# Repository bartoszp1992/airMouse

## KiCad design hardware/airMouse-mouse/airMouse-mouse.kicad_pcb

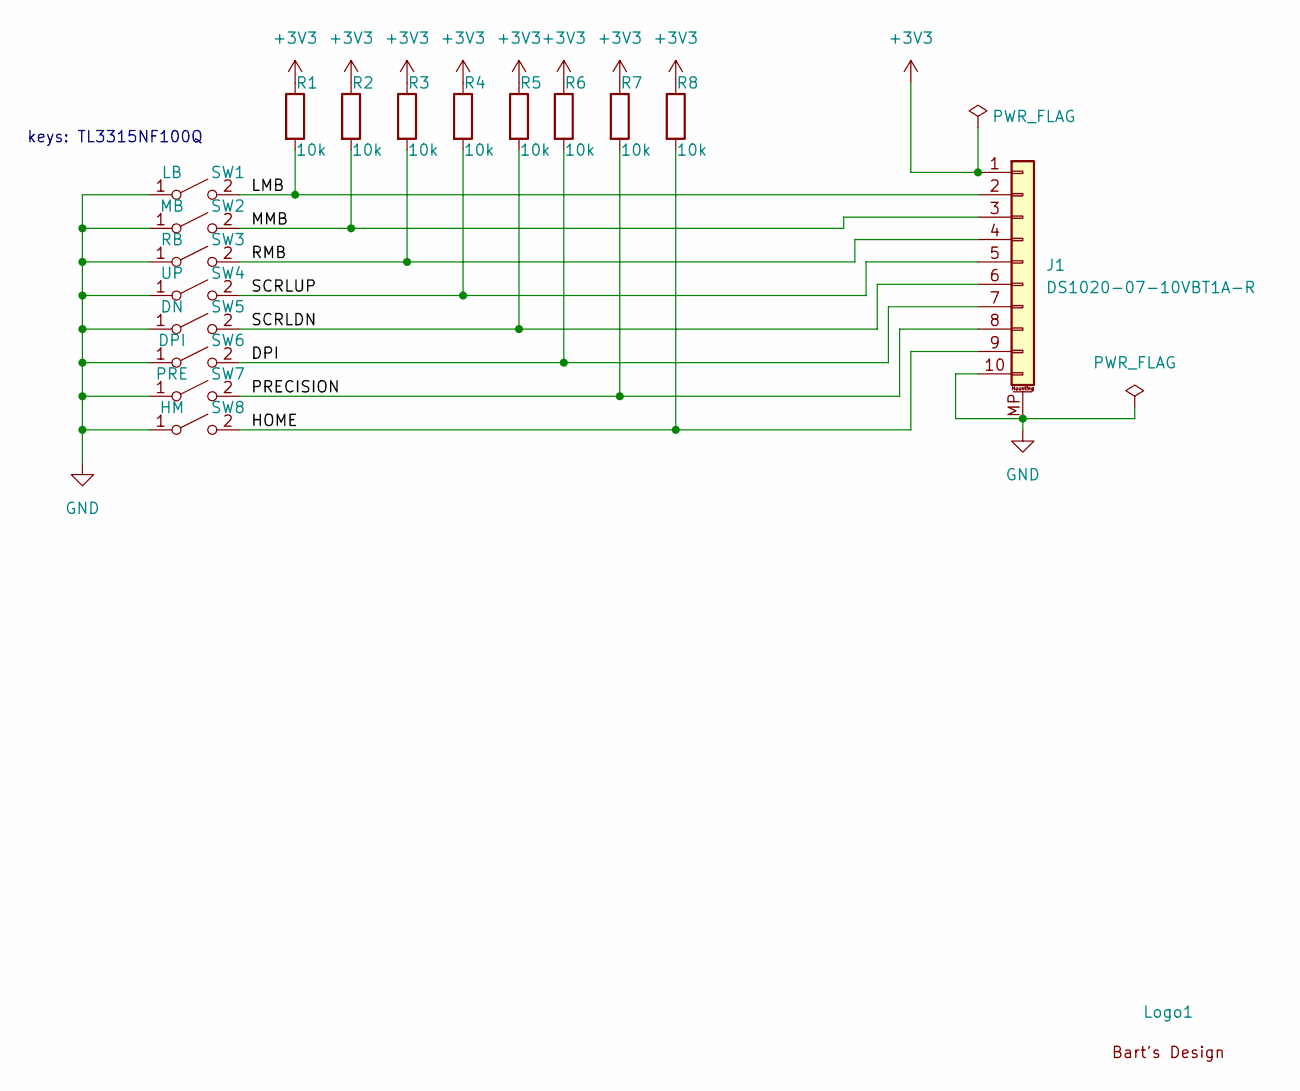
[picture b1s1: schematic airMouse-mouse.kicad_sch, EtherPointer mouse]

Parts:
J1: DS1020-07-10VBT1A-R
Logo1: Bart's Design 30mm
R1, R2, R3, R4, R5, R6, R7, R8: 10k; R_0603_1608Metric
SW1, SW2, SW3, SW4, SW5, SW6, SW7, SW8: KEY; TL3315NF100Q

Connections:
+3V3: J1.1, R1.1, R2.1, R3.1, R4.1, R5.1, R6.1, R7.1, R8.1
/DPI: J1.7, R6.2, SW6.2 (B)
/HOME: J1.9, R8.2, SW8.2 (B)
/LMB: J1.2, R1.2, SW1.2 (B)
/MMB: J1.3, R2.2, SW2.2 (B)
/PRECISION: J1.8, R7.2, SW7.2 (B)
/RMB: J1.4, R3.2, SW3.2 (B)
/SCRLDN: J1.6, R5.2, SW5.2 (B)
/SCRLUP: J1.5, R4.2, SW4.2 (B)
GND: J1.10, J1.MP (MountPin), SW1.1 (A), SW2.1 (A), SW3.1 (A), SW4.1 (A), SW5.1 (A), SW6.1 (A), SW7.1 (A), SW8.1 (A)

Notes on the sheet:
keys: TL3315NF100Q

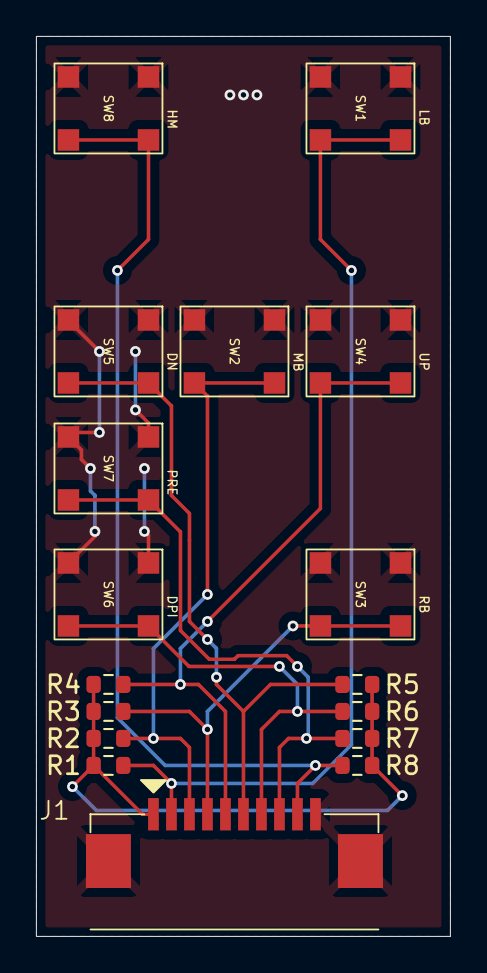
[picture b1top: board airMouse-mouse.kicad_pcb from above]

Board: 2 copper layers, 23.0 x 50.0 mm, 18 parts (1 on the bottom side), 10 nets.

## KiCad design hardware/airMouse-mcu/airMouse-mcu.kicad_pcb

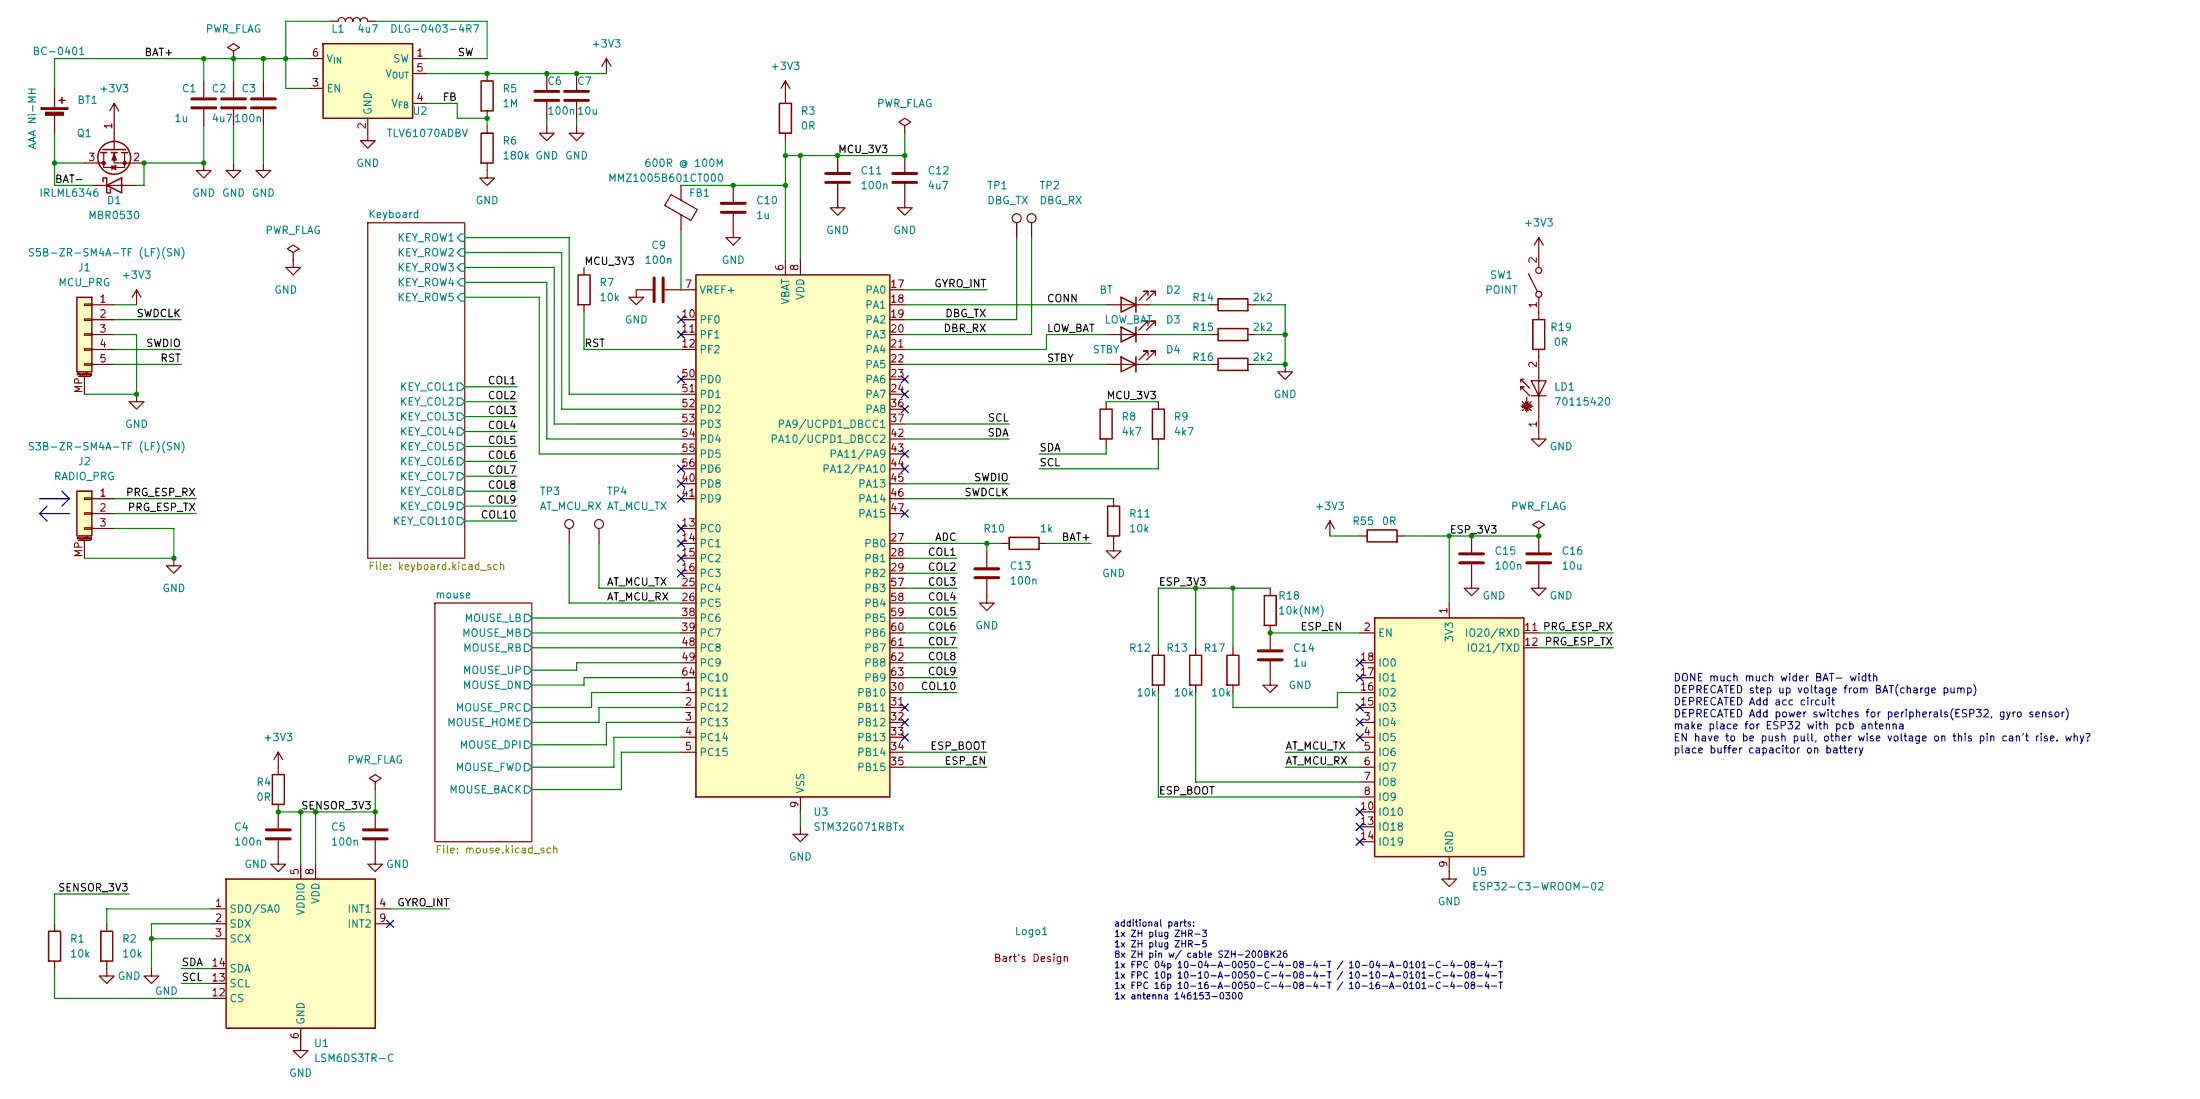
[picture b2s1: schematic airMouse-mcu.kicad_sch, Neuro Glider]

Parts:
BT1: BC-0401
C1, C10, C14: 1u; C_0603_1608Metric
C2, C12: 4u7; C_0805_2012Metric
C3, C4, C5, C6, C9, C11, C13, C15: 100n; C_0603_1608Metric
C7, C16: 10u; C_0805_2012Metric
D1: MBR0530; D_SOD-123
D2: BT; LED_0603_1608Metric
D3: LOW_BAT; LED_0603_1608Metric
D4: STBY; LED_0603_1608Metric
FB1: 600R @ 100M; C_0603_1608Metric
J1: MCU_PRG; JST_ZH_S5B-ZR-SM4A-TF_1x05-1MP_P1.50mm_Horizontal
J2: RADIO_PRG; JST_ZH_S3B-ZR-SM4A-TF_1x03-1MP_P1.50mm_Horizontal
L1: 4u7; L_Ferrocore_DLG-0403
LD1: 70115420; PinHeader_1x02_P2.54mm_Vertical
Logo1: Bart's Design 30mm
Q1: IRLML6346; SOT-23
R1, R2, R7, R11, R12, R13, R17: 10k; R_0603_1608Metric
R3, R4, R19, R55: 0R; R_0603_1608Metric
R5: 1M; R_0603_1608Metric
R6: 180k; R_0603_1608Metric
R8, R9: 4k7; R_0603_1608Metric
R10: 1k; R_0603_1608Metric
R14, R15, R16: 2k2; R_0603_1608Metric
R18: 10k(NM); R_0603_1608Metric
SW1: KEY; TL3315NF100Q
TP1: DBG_TX; TestPoint_Pad_D1.0mm
TP2: DBG_RX; TestPoint_Pad_D1.0mm
TP3: AT_MCU_RX; TestPoint_Pad_D1.0mm
TP4: AT_MCU_TX; TestPoint_Pad_D1.0mm
U1: LSM6DS3TR-C; LGA-14_3x2.5mm_P0.5mm_LayoutBorder3x4y
U2: TLV61070ADBV; SOT-23-6
U3: STM32G071RBTx; LQFP-64_10x10mm_P0.5mm
U5: ESP32-C3-WROOM-02

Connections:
+3V3: C6.1, C7.1, J1.1, Q1.1 (G), R3.1, R4.1, R5.1, R55.1, SW1.2 (B), U2.5 (V_{OUT}); also elsewhere on the board
/ADC: C13.1, R10.1, U3.27 (PB0)
/AT_MCU_RX: TP3.1, U3.26 (PC5), U5.6 (IO7)
/AT_MCU_TX: TP4.1, U3.25 (PC4), U5.5 (IO6)
/BAT+: BT1.1 (+), C1.1, C2.1, C3.1, L1.1, R10.2, U2.3 (EN), U2.6 (V_{IN})
/BAT-: BT1.2 (-), D1.1 (K), Q1.3 (D)
/COL1: U3.28 (PB1); also elsewhere on the board
/COL2: U3.29 (PB2); also elsewhere on the board
/COL3: U3.57 (PB3); also elsewhere on the board
/COL4: U3.58 (PB4); also elsewhere on the board
/COL5: U3.59 (PB5); also elsewhere on the board
/COL6: U3.60 (PB6); also elsewhere on the board
/COL7: U3.61 (PB7); also elsewhere on the board
/COL8: U3.62 (PB8); also elsewhere on the board
/COL9: U3.63 (PB9); also elsewhere on the board
/COL10: U3.30 (PB10); also elsewhere on the board
/CONN: D2.2 (A), U3.18 (PA1)
/DBG_TX: TP1.1, U3.19 (PA2)
/DBR_RX: TP2.1, U3.20 (PA3)
/ESP_3V3: C15.1, C16.1, R12.1, R13.1, R17.1, R18.1, R55.2, U5.1 (3V3)
/ESP_BOOT: R12.2, U3.34 (PB14), U5.8 (IO9)
/ESP_EN: C14.1, R18.2, U3.35 (PB15), U5.2 (EN)
/FB: R5.2, R6.1, U2.4 (V_{FB})
/GYRO_INT: U1.4 (INT1), U3.17 (PA0)
/Keyboard/KEY_ROW1: U3.51 (PD1); also elsewhere on the board
/Keyboard/KEY_ROW2: U3.52 (PD2); also elsewhere on the board
/Keyboard/KEY_ROW3: U3.53 (PD3); also elsewhere on the board
/Keyboard/KEY_ROW4: U3.54 (PD4); also elsewhere on the board
/Keyboard/KEY_ROW5: U3.55 (PD5); also elsewhere on the board
/LOW_BAT: D3.2 (A), U3.21 (PA4)
/MCU_3V3: C10.1, C11.1, C12.1, FB1.1, R3.2, R7.1, R8.1, R9.1, U3.6 (VBAT), U3.8 (VDD)
/PRG_ESP_RX: J2.1, U5.11 (IO20/RXD)
/PRG_ESP_TX: J2.2, U5.12 (IO21/TXD)
/RST: J1.5, R7.2, U3.12 (PF2)
/SCL: R9.2, U1.13 (SCL), U3.37 (PA9/UCPD1_DBCC1)
/SDA: R8.2, U1.14 (SDA), U3.42 (PA10/UCPD1_DBCC2)
/SENSOR_3V3: C4.1, C5.1, R1.1, R4.2, U1.5 (VDDIO), U1.8 (VDD)
/STBY: D4.2 (A), U3.22 (PA5)
/SW: L1.2, U2.1 (SW)
/SWDCLK: J1.2, R11.1, U3.46 (PA14)
/SWDIO: J1.4, U3.45 (PA13)
/mouse/MOUSE_BACK: U3.5 (PC15); also elsewhere on the board
/mouse/MOUSE_DN: U3.64 (PC10); also elsewhere on the board
/mouse/MOUSE_DPI: U3.3 (PC13); also elsewhere on the board
/mouse/MOUSE_FWD: U3.4 (PC14); also elsewhere on the board
/mouse/MOUSE_HOME: U3.2 (PC12); also elsewhere on the board
/mouse/MOUSE_LB: U3.38 (PC6); also elsewhere on the board
/mouse/MOUSE_MB: U3.39 (PC7); also elsewhere on the board
/mouse/MOUSE_PRC: U3.1 (PC11); also elsewhere on the board
/mouse/MOUSE_RB: U3.48 (PC8); also elsewhere on the board
/mouse/MOUSE_UP: U3.49 (PC9); also elsewhere on the board
GND: C1.2, C2.2, C3.2, C4.2, C5.2, C6.2, C7.2, C9.2, C10.2, C11.2, C12.2, C13.2, C14.2, C15.2, C16.2, D1.2 (A), J1.3, J1.MP (MountPin), J2.3, J2.MP (MountPin), LD1.1 (K), Q1.2 (S), R2.2, R6.2, R11.2, R14.2, R15.2, R16.2, U1.2 (SDX), U1.3 (SCX), U1.6 (GND), U1.7 (GND), U2.2 (GND), U3.9 (VSS), U5.9 (GND), U5.19 (GND); also elsewhere on the board
unnamed: D2.1 (K), R14.1
unnamed: D3.1 (K), R15.1
unnamed: D4.1 (K), R16.1
unnamed: LD1.2 (A), R19.1
unnamed: R19.2, SW1.1 (A)
unnamed: R1.2, U1.12 (CS)
unnamed: R2.1, U1.1 (SDO/SA0)
unnamed: C9.1, FB1.2, U3.7 (VREF+)
unnamed: R17.2, U5.16 (IO2)
unnamed: R13.2, U5.7 (IO8)

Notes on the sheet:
additional parts: 1x ZH plug ZHR-3 1x ZH plug ZHR-5 8x ZH pin w/ cable SZH-200BK26 1x FPC 04p 10-04-A-0050-C-4-08-4-T / 10-04-A-0101-C-4-08-4-T 1x FPC 10p 10-10-A-0050-C-4-08-4-T / 10-10-A-0101-C-4-08-4-T 1x FPC 16p 10-16-A-0050-C-4-08-4-T / 10-16-A-0101-C-4-08-4-T 1x antenna 146153-0300
DONE much much wider BAT- width DEPRECATED step up voltage from BAT(charge pump) DEPRECATED Add acc circuit DEPRECATED Add power switches for peripherals(ESP32, gyro sensor) make place for ESP32 with pcb antenna EN have to be push pull, other wise voltage on this pin can't rise. why? place buffer c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

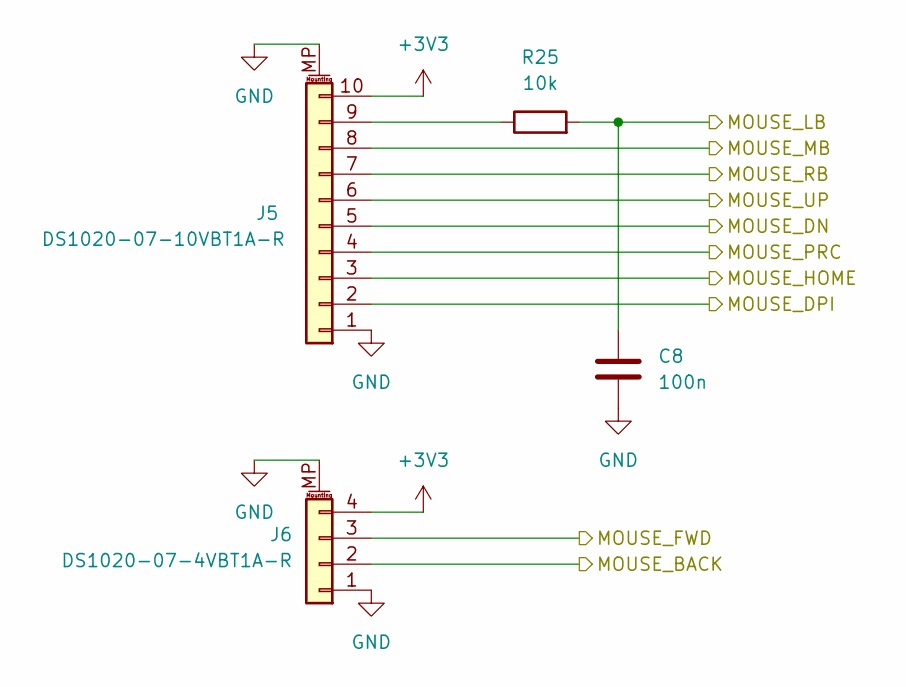
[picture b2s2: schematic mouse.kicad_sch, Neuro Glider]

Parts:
C8: 100n; C_0603_1608Metric
J5: DS1020-07-10VBT1A-R
J6: DS1020-07-4VBT1A-R
R25: 10k; R_0603_1608Metric

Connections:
+3V3: J5.10, J6.4; also elsewhere on the board
/mouse/MOUSE_BACK: J6.2; also elsewhere on the board
/mouse/MOUSE_DN: J5.5; also elsewhere on the board
/mouse/MOUSE_DPI: J5.2; also elsewhere on the board
/mouse/MOUSE_FWD: J6.3; also elsewhere on the board
/mouse/MOUSE_HOME: J5.3; also elsewhere on the board
/mouse/MOUSE_LB: C8.1, R25.2; also elsewhere on the board
/mouse/MOUSE_MB: J5.8; also elsewhere on the board
/mouse/MOUSE_PRC: J5.4; also elsewhere on the board
/mouse/MOUSE_RB: J5.7; also elsewhere on the board
/mouse/MOUSE_UP: J5.6; also elsewhere on the board
GND: C8.2, J5.1, J5.MP (MountPin), J6.1, J6.MP (MountPin); also elsewhere on the board
unnamed: J5.9, R25.1

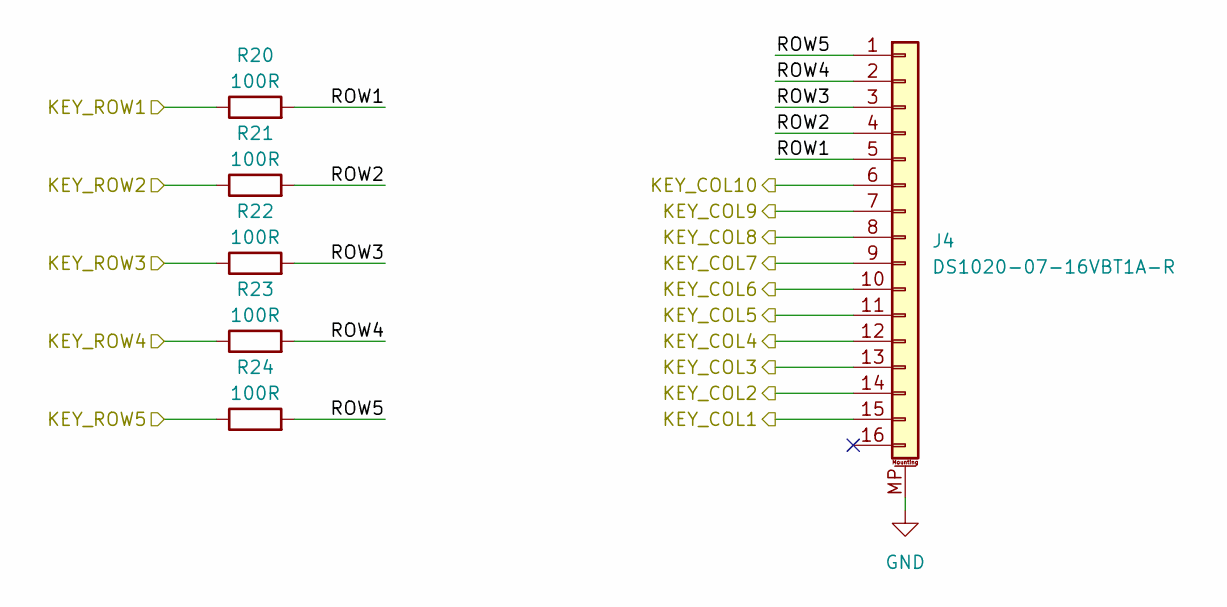
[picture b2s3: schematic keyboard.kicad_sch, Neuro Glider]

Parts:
J4: DS1020-07-16VBT1A-R
R20, R21, R22, R23, R24: 100R; R_0603_1608Metric

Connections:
/COL1: J4.15; also elsewhere on the board
/COL2: J4.14; also elsewhere on the board
/COL3: J4.13; also elsewhere on the board
/COL4: J4.12; also elsewhere on the board
/COL5: J4.11; also elsewhere on the board
/COL6: J4.10; also elsewhere on the board
/COL7: J4.9; also elsewhere on the board
/COL8: J4.8; also elsewhere on the board
/COL9: J4.7; also elsewhere on the board
/COL10: J4.6; also elsewhere on the board
/Keyboard/KEY_ROW1: R20.1; also elsewhere on the board
/Keyboard/KEY_ROW2: R21.1; also elsewhere on the board
/Keyboard/KEY_ROW3: R22.1; also elsewhere on the board
/Keyboard/KEY_ROW4: R23.1; also elsewhere on the board
/Keyboard/KEY_ROW5: R24.1; also elsewhere on the board
/Keyboard/ROW1: J4.5, R20.2
/Keyboard/ROW2: J4.4, R21.2
/Keyboard/ROW3: J4.3, R22.2
/Keyboard/ROW4: J4.2, R23.2
/Keyboard/ROW5: J4.1, R24.2
GND: J4.MP (MountPin); also elsewhere on the board

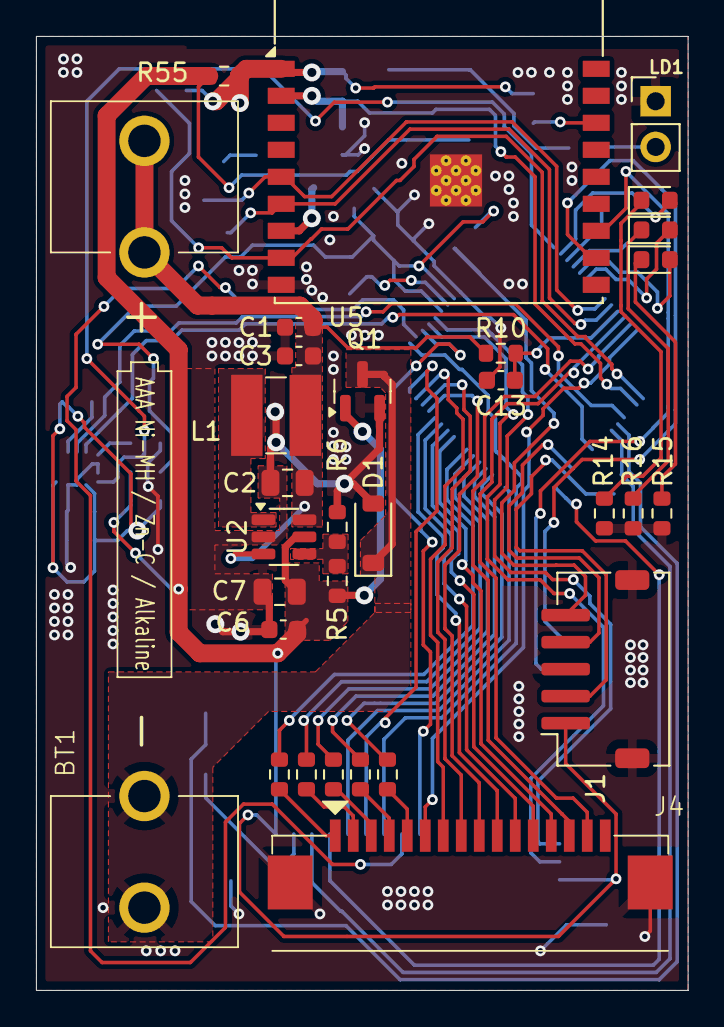
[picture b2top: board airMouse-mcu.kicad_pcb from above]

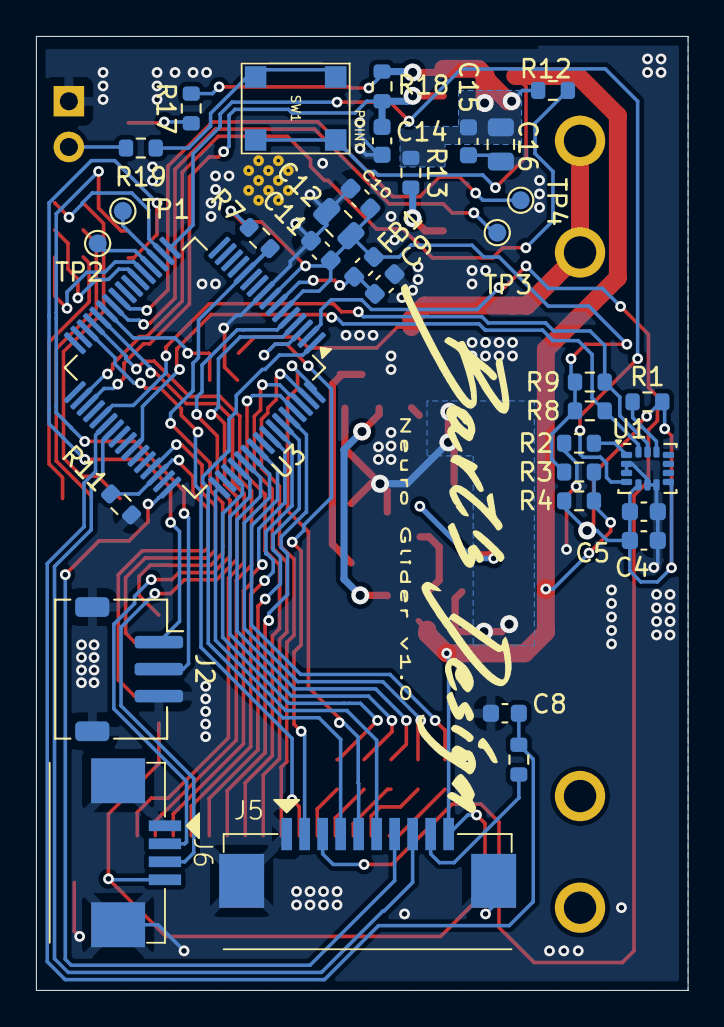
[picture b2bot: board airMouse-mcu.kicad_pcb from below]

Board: 2 copper layers, 36.2 x 53.0 mm, 66 parts (36 on the bottom side), 68 nets.

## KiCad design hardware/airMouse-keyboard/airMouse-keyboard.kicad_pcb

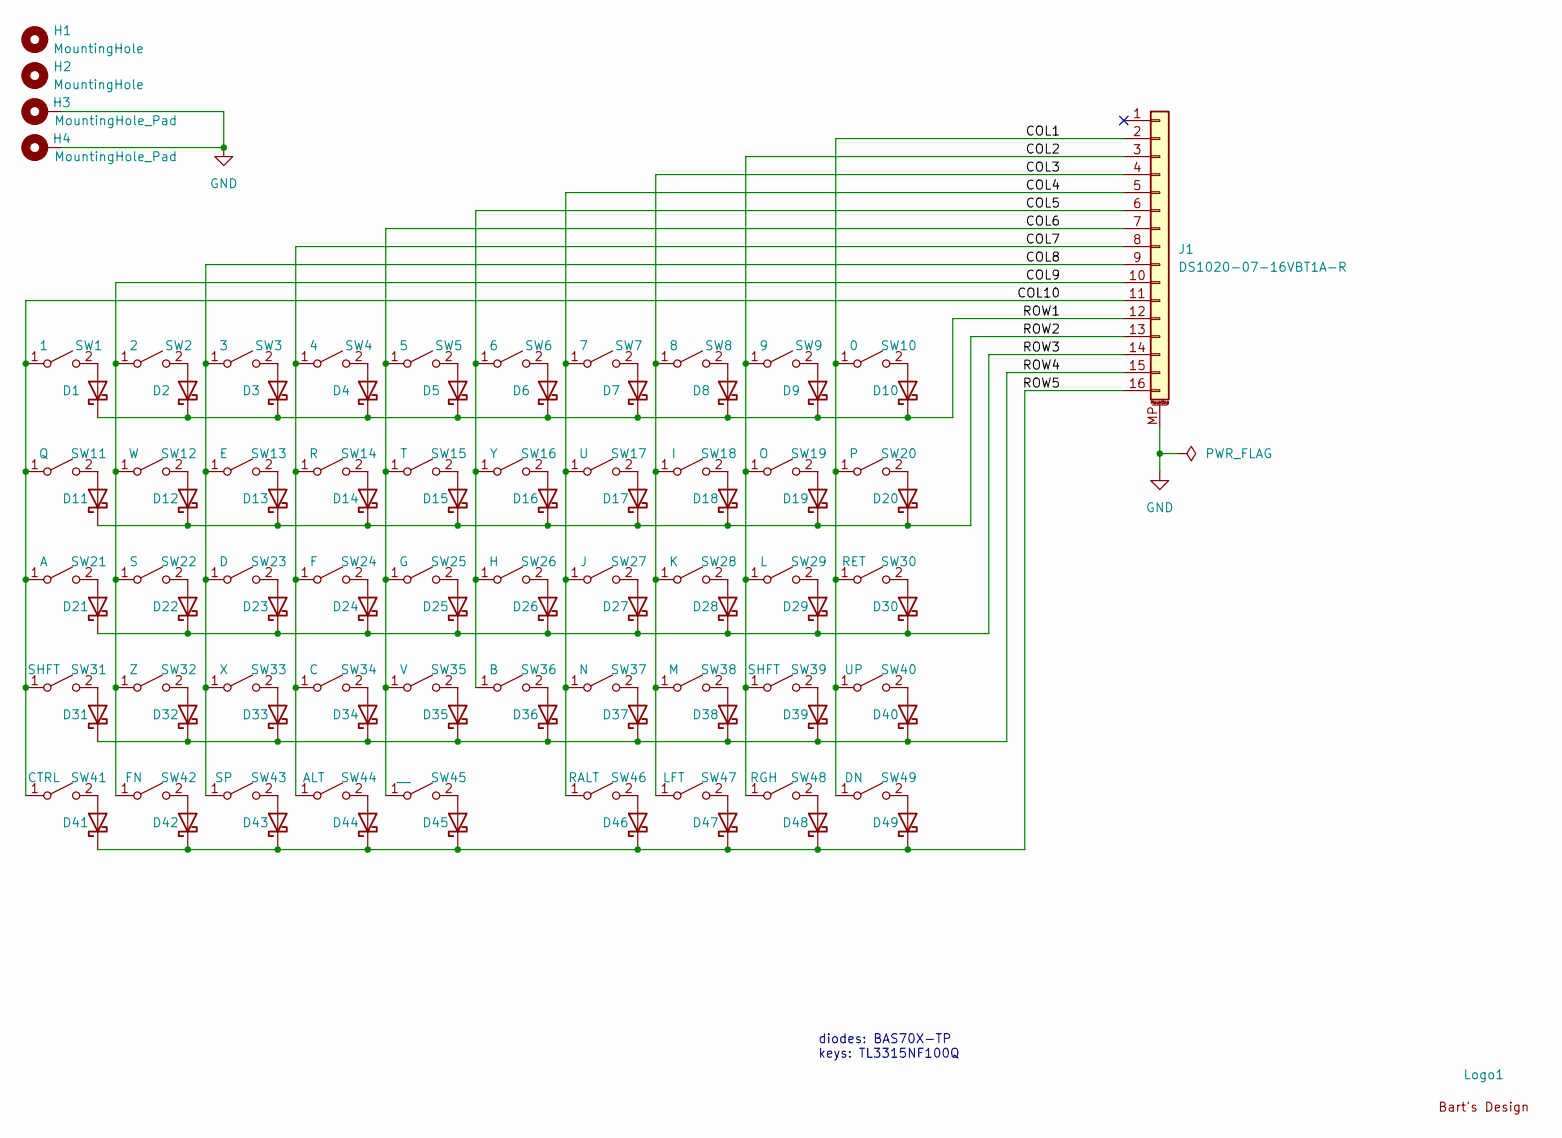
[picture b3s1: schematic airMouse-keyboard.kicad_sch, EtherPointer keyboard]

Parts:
D1, D2, D3, D4, D5, D6, D7, D8, D9, D10, D11, D12, D13, D14, D15, D16, D17, D18, D19, D20, D21, D22, D23, D24, D25, D26, D27, D28, D29, D30, D31, D32, D33, D34, D35, D36, D37, D38, D39, D40, D41, D42, D43, D44, D45, D46, D47, D48, D49: BAS70X-TP; D_SOD-523
H1, H2: MountingHole; MountingHole_2.2mm_M2_ISO14580
H3, H4: MountingHole_Pad; MountingHole_2.2mm_M2_ISO14580_Pad
J1: DS1020-07-16VBT1A-R
Logo1: Bart's Design 30mm
SW1, SW2, SW3, SW4, SW5, SW6, SW7, SW8, SW9, SW10, SW11, SW12, SW13, SW14, SW15, SW16, SW17, SW18, SW19, SW20, SW21, SW22, SW23, SW24, SW25, SW26, SW27, SW28, SW29, SW30, SW31, SW32, SW33, SW34, SW35, SW36, SW37, SW38, SW39, SW40, SW41, SW42, SW43, SW44, SW45, SW46, SW47, SW48, SW49: KEY; TL3315NF100Q

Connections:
/COL1: J1.2, SW10.1 (A), SW20.1 (A), SW30.1 (A), SW40.1 (A), SW49.1 (A)
/COL2: J1.3, SW9.1 (A), SW19.1 (A), SW29.1 (A), SW39.1 (A), SW48.1 (A)
/COL3: J1.4, SW8.1 (A), SW18.1 (A), SW28.1 (A), SW38.1 (A), SW47.1 (A)
/COL4: J1.5, SW7.1 (A), SW17.1 (A), SW27.1 (A), SW37.1 (A), SW46.1 (A)
/COL5: J1.6, SW6.1 (A), SW16.1 (A), SW26.1 (A), SW36.1 (A)
/COL6: J1.7, SW5.1 (A), SW15.1 (A), SW25.1 (A), SW35.1 (A), SW45.1 (A)
/COL7: J1.8, SW4.1 (A), SW14.1 (A), SW24.1 (A), SW34.1 (A), SW44.1 (A)
/COL8: J1.9, SW3.1 (A), SW13.1 (A), SW23.1 (A), SW33.1 (A), SW43.1 (A)
/COL9: J1.10, SW2.1 (A), SW12.1 (A), SW22.1 (A), SW32.1 (A), SW42.1 (A)
/COL10: J1.11, SW1.1 (A), SW11.1 (A), SW21.1 (A), SW31.1 (A), SW41.1 (A)
/ROW1: D1.1 (K), D2.1 (K), D3.1 (K), D4.1 (K), D5.1 (K), D6.1 (K), D7.1 (K), D8.1 (K), D9.1 (K), D10.1 (K), J1.12
/ROW2: D11.1 (K), D12.1 (K), D13.1 (K), D14.1 (K), D15.1 (K), D16.1 (K), D17.1 (K), D18.1 (K), D19.1 (K), D20.1 (K), J1.13
/ROW3: D21.1 (K), D22.1 (K), D23.1 (K), D24.1 (K), D25.1 (K), D26.1 (K), D27.1 (K), D28.1 (K), D29.1 (K), D30.1 (K), J1.14
/ROW4: D31.1 (K), D32.1 (K), D33.1 (K), D34.1 (K), D35.1 (K), D36.1 (K), D37.1 (K), D38.1 (K), D39.1 (K), D40.1 (K), J1.15
/ROW5: D41.1 (K), D42.1 (K), D43.1 (K), D44.1 (K), D45.1 (K), D46.1 (K), D47.1 (K), D48.1 (K), D49.1 (K), J1.16
GND: H3.1, H4.1, J1.MP (MountPin)
unnamed: D1.2 (A), SW1.2 (B)
unnamed: D2.2 (A), SW2.2 (B)
unnamed: D3.2 (A), SW3.2 (B)
unnamed: D4.2 (A), SW4.2 (B)
unnamed: D5.2 (A), SW5.2 (B)
unnamed: D6.2 (A), SW6.2 (B)
unnamed: D7.2 (A), SW7.2 (B)
unnamed: D8.2 (A), SW8.2 (B)
unnamed: D9.2 (A), SW9.2 (B)
unnamed: D10.2 (A), SW10.2 (B)
unnamed: D11.2 (A), SW11.2 (B)
unnamed: D12.2 (A), SW12.2 (B)
unnamed: D13.2 (A), SW13.2 (B)
unnamed: D14.2 (A), SW14.2 (B)
unnamed: D15.2 (A), SW15.2 (B)
unnamed: D16.2 (A), SW16.2 (B)
unnamed: D17.2 (A), SW17.2 (B)
unnamed: D18.2 (A), SW18.2 (B)
unnamed: D19.2 (A), SW19.2 (B)
unnamed: D20.2 (A), SW20.2 (B)
unnamed: D21.2 (A), SW21.2 (B)
unnamed: D22.2 (A), SW22.2 (B)
unnamed: D23.2 (A), SW23.2 (B)
unnamed: D24.2 (A), SW24.2 (B)
unnamed: D25.2 (A), SW25.2 (B)
unnamed: D26.2 (A), SW26.2 (B)
unnamed: D27.2 (A), SW27.2 (B)
unnamed: D28.2 (A), SW28.2 (B)
unnamed: D29.2 (A), SW29.2 (B)
unnamed: D30.2 (A), SW30.2 (B)
unnamed: D31.2 (A), SW31.2 (B)
unnamed: D32.2 (A), SW32.2 (B)
unnamed: D33.2 (A), SW33.2 (B)
unnamed: D34.2 (A), SW34.2 (B)
unnamed: D35.2 (A), SW35.2 (B)
unnamed: D36.2 (A), SW36.2 (B)
unnamed: D37.2 (A), SW37.2 (B)
unnamed: D38.2 (A), SW38.2 (B)
unnamed: D39.2 (A), SW39.2 (B)
unnamed: D40.2 (A), SW40.2 (B)
unnamed: D41.2 (A), SW41.2 (B)
unnamed: D42.2 (A), SW42.2 (B)
unnamed: D43.2 (A), SW43.2 (B)
unnamed: D44.2 (A), SW44.2 (B)
unnamed: D45.2 (A), SW45.2 (B)
unnamed: D46.2 (A), SW46.2 (B)
unnamed: D47.2 (A), SW47.2 (B)
unnamed: D48.2 (A), SW48.2 (B)
unnamed: D49.2 (A), SW49.2 (B)

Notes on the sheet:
diodes: BAS70X-TP keys: TL3315NF100Q

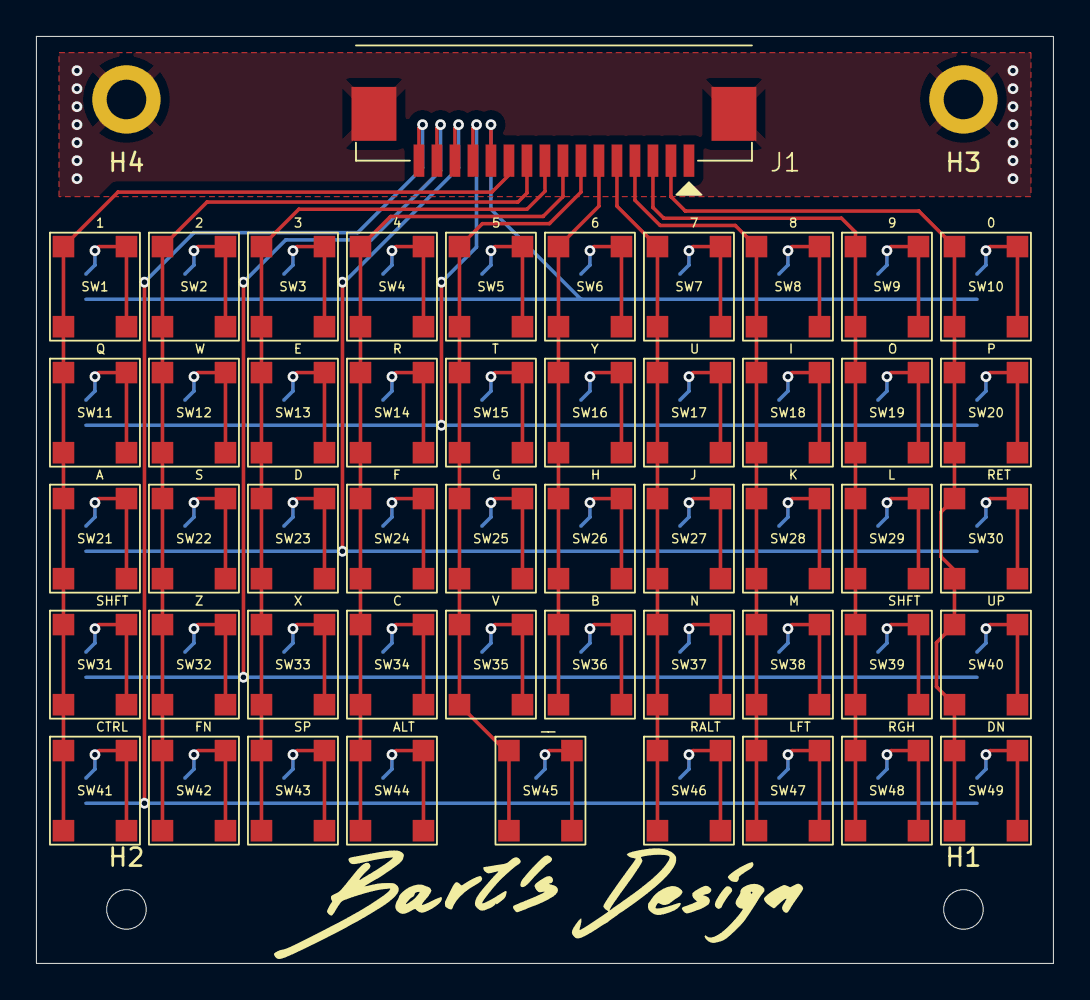
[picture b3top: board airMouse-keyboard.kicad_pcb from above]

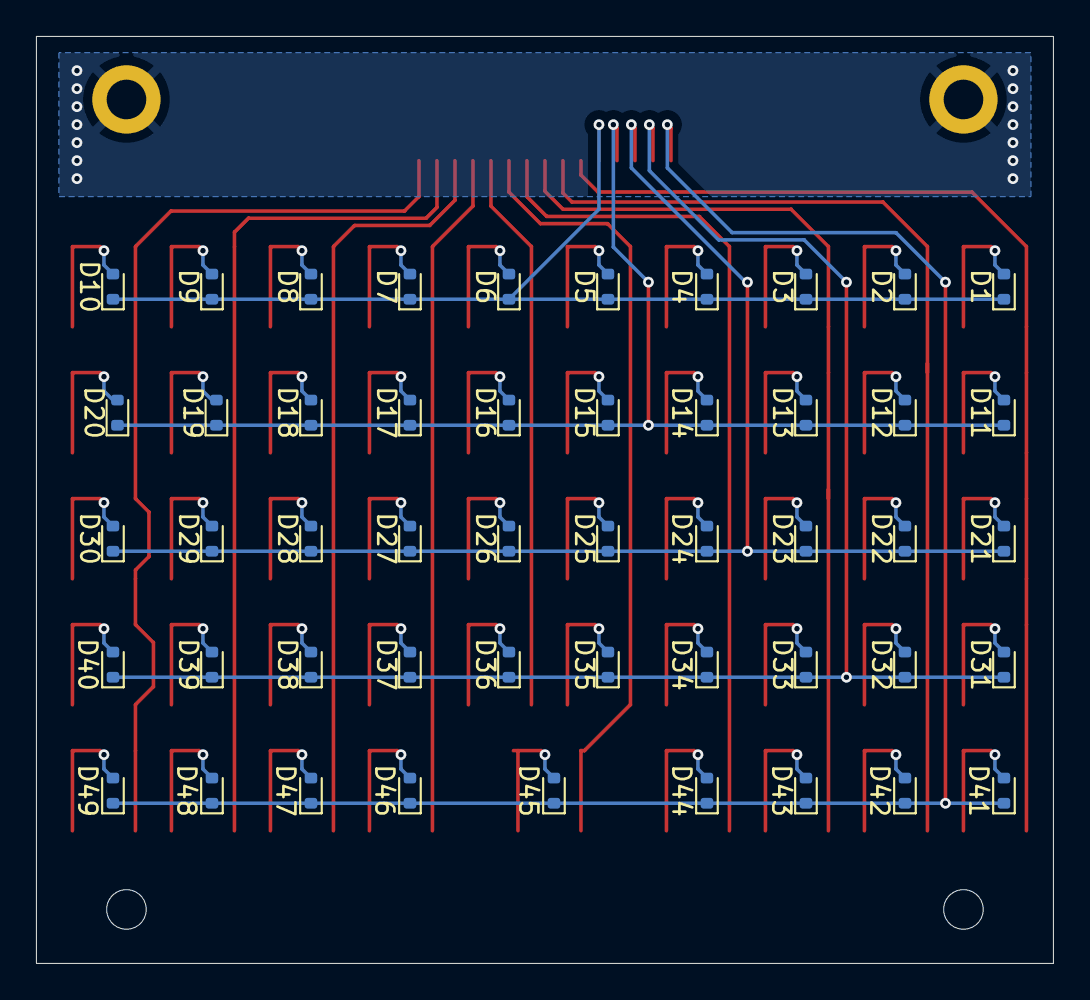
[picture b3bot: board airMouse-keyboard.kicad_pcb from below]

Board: 2 copper layers, 56.5 x 51.5 mm, 104 parts (49 on the bottom side), 65 nets.
